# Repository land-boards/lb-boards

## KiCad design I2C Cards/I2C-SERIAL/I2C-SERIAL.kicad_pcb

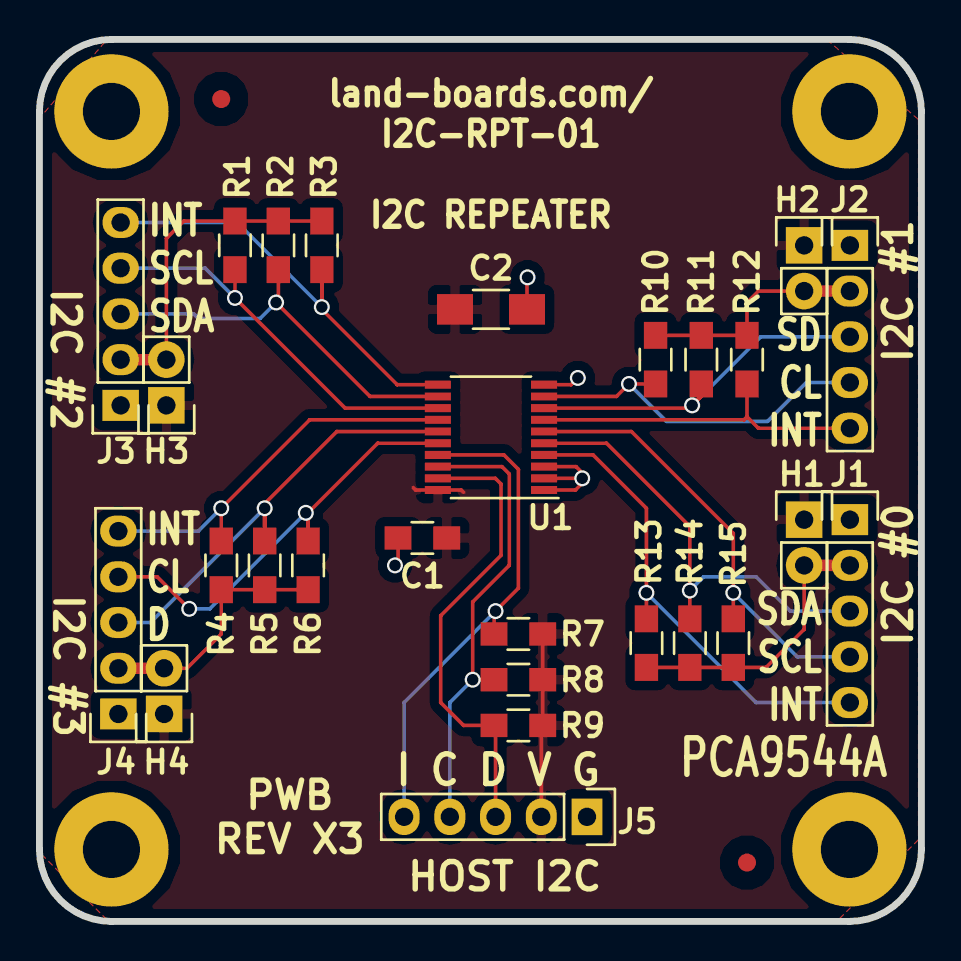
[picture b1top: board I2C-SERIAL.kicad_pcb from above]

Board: 2 copper layers, 49.0 x 49.0 mm, 35 parts (1 on the bottom side), 21 nets.

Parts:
C1: 0.1uF; R_0805_HandSoldering
C2: 0.1uF; R_1206_HandSoldering
FID1, FID2: ADAFRUIT_FIDUCIAL; FIDUCIAL
H1, H2, H3, H4: CONN_01X02; Pin_Header_Straight_1x02
J1, J2, J3, J4, J5: I2CINT-5PIN; Pin_Header_Straight_1x05
MTG1, MTG2, MTG3, MTG4: MTG_HOLE; MTG-4-40
R1, R2, R3, R4, R5, R6, R7, R8, R9, R10, R11, R12, R13, R14, R15: 3.3K; R_0805_HandSoldering
ST1: CONN_1; REV_BLOCK
TESTED: VAL**; TEST_BLK-REAR
U1: PCA9544A; TSSOP-20_4.4x6.5mm_Pitch0.65mm

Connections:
/PWR: C1.1, C2.1, H1.1, H2.1, H3.1, H4.1, J5.2, R7.1, R8.1, R9.1, U1.20
/SCK0: J1.4, R15.2, U1.6
/SCK1: J2.4, R10.2, U1.9
/SCK2: J3.4, R1.2, U1.13
/SCK3: J4.4, R6.2, U1.16
/SDA0: J1.3, R14.2, U1.5
/SDA1: J2.3, R11.2, U1.8
/SDA2: J3.3, R2.2, U1.12
/SDA3: J4.3, R5.2, U1.15
/~I0: J1.5, R13.2, U1.4
/~I1: J2.5, R12.2, U1.7
/~I2: J3.5, R3.2, U1.11
/~I3: J4.5, R4.2, U1.14
/~IH: J5.5, R7.2, U1.17
GND: C1.2, C2.2, J1.1, J2.1, J3.1, J4.1, J5.1, U1.1, U1.2, U1.3, U1.10
unnamed: H1.2, J1.2, R13.1, R14.1, R15.1
unnamed: H2.2, J2.2, R10.1, R11.1, R12.1
unnamed: H3.2, J3.2, R1.1, R2.1, R3.1
unnamed: H4.2, J4.2, R4.1, R5.1, R6.1
unnamed: J5.3, R9.2, U1.19
unnamed: J5.4, R8.2, U1.18

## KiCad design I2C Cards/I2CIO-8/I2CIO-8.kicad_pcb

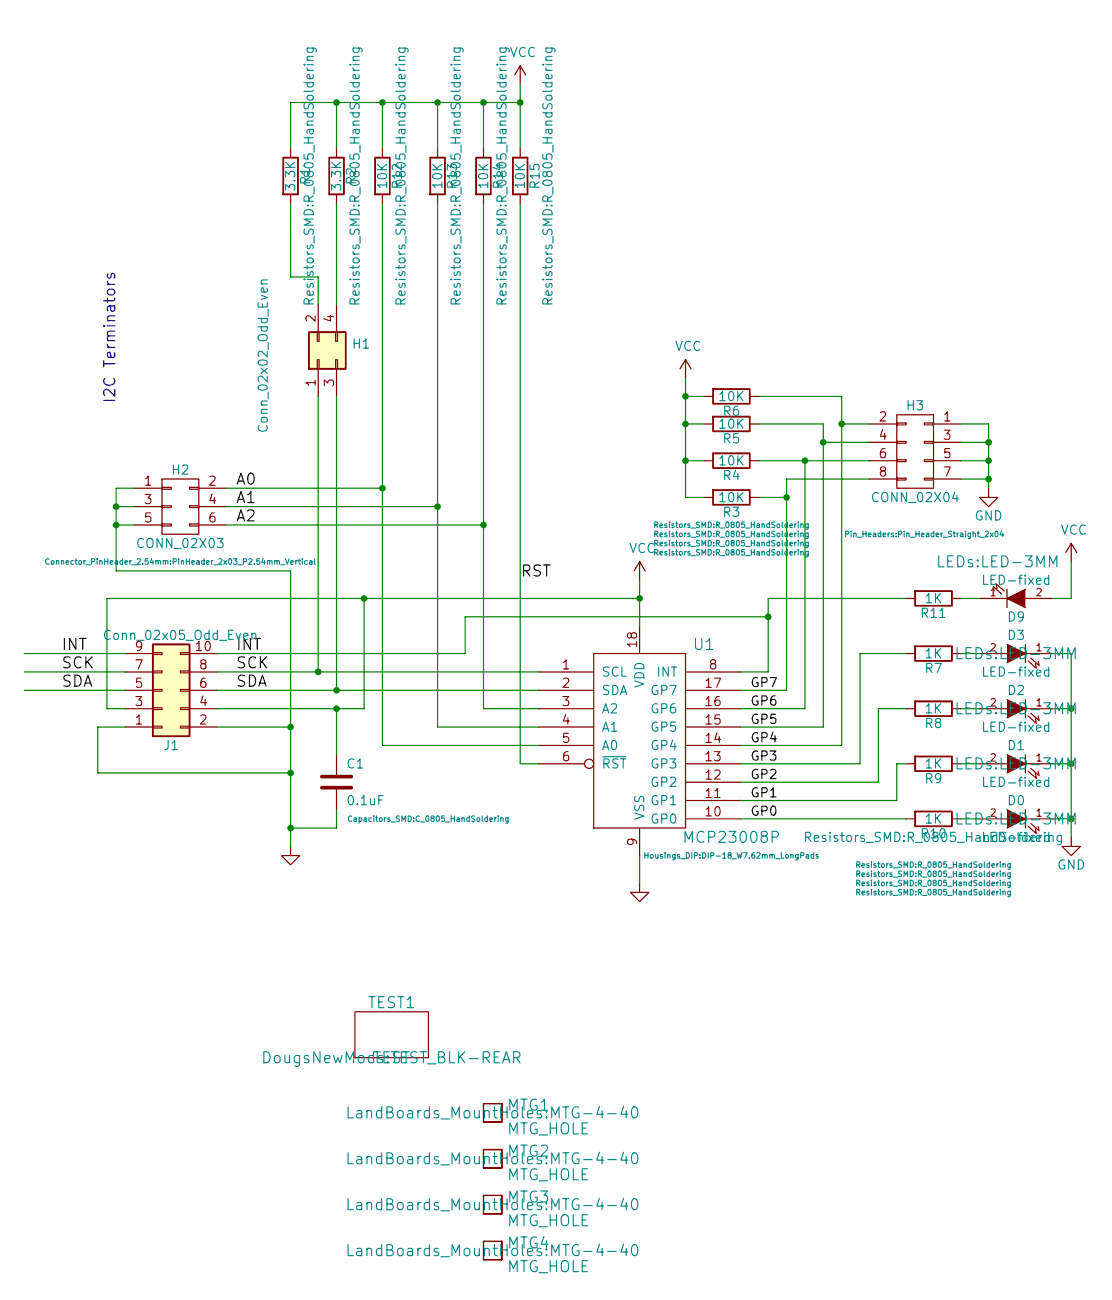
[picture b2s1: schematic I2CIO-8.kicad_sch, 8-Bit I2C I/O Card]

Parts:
C1: 0.1uF; C_0805_HandSoldering
D0, D1, D2, D3, D9: LED-fixed; LED-3MM
H1: Conn_02x02_Odd_Even; PinHeader_2x02_P2.54mm_Vertical
H2: CONN_02X03; PinHeader_2x03_P2.54mm_Vertical
H3: CONN_02X04; Pin_Header_Straight_2x04
J1: Conn_02x05_Odd_Even; PinHeader_2x05_P2.54mm_Horizontal
MTG1, MTG2, MTG3, MTG4: MTG_HOLE; MTG-4-40
R1, R2: 3.3K; R_0805_HandSoldering
R3, R4, R5, R6, R12, R13, R14, R15: 10K; R_0805_HandSoldering
R7, R8, R9, R10, R11: 1K; R_0805_HandSoldering
TEST1: TEST; TEST_BLK-REAR
U1: MCP23008P; DIP-18_W7.62mm_LongPads

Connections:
/A0: H2.2, R12.2, U1.5 (A0)
/A1: H2.4, R13.2, U1.4 (A1)
/A2: H2.6, R14.2, U1.3 (A2)
/GP0: R10.2, U1.10 (GP0)
/GP1: R9.2, U1.11 (GP1)
/GP2: R8.2, U1.12 (GP2)
/GP3: R7.2, U1.13 (GP3)
/GP4: H3.2, R6.1, U1.14 (GP4)
/GP5: H3.4, R5.1, U1.15 (GP5)
/GP6: H3.6, R4.1, U1.16 (GP6)
/GP7: H3.8, R3.1, U1.17 (GP7)
/INT: J1.9, J1.10, R11.2, U1.8 (INT)
/RST: R15.2, U1.6 (~RST)
/SCK: H1.1, J1.7, J1.8, U1.1 (SCL)
/SDA: H1.3, J1.5, J1.6, U1.2 (SDA)
GND: C1.2, D0.1 (K), D1.1 (K), D2.1 (K), D3.1 (K), H2.1, H2.3, H2.5, H3.1, H3.3, H3.5, H3.7, J1.1, J1.2, U1.9 (VSS)
unnamed: D0.2 (A), R10.1
unnamed: D1.2 (A), R9.1
unnamed: D2.2 (A), R8.1
unnamed: D3.2 (A), R7.1
unnamed: H1.2, R1.2
unnamed: H1.4, R2.2
unnamed: D9.1 (K), R11.1
VCC: C1.1, D9.2 (A), J1.3, J1.4, R1.1, R2.1, R3.2, R4.2, R5.2, R6.2, R12.1, R13.1, R14.1, R15.1, U1.18 (VDD)

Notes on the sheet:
I2C Terminators

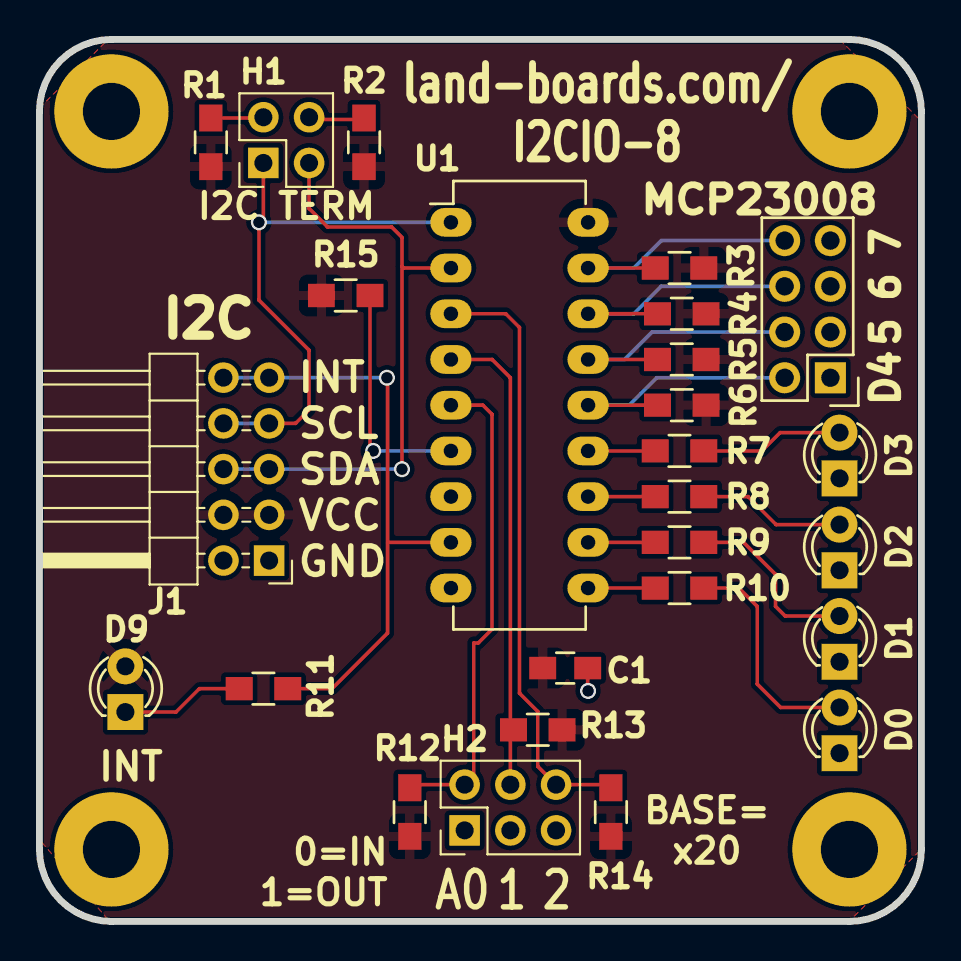
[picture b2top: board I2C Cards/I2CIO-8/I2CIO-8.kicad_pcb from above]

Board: 2 copper layers, 49.0 x 49.0 mm, 31 parts (0 on the bottom side), 24 nets.

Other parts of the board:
TEST: TEST; TEST_BLK-REAR

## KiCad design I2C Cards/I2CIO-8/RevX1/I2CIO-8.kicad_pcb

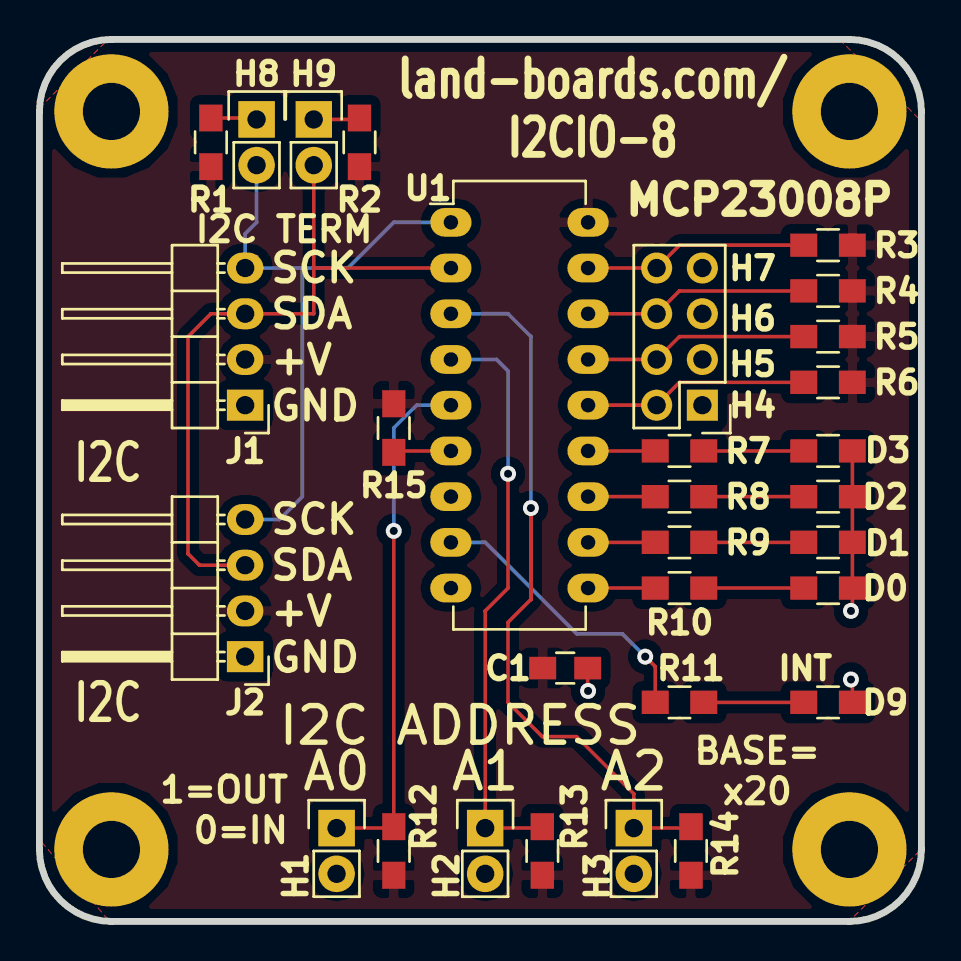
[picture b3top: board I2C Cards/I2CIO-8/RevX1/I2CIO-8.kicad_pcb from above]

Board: 2 copper layers, 49.0 x 49.0 mm, 35 parts (0 on the bottom side), 24 nets.

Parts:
C1: 0.1uF; C_0805_HandSoldering
D0, D1, D2, D3, D9: LED; R_0805_HandSoldering
H1, H2, H3, H8, H9: CONN_2; Pin_Header_Straight_1x02
H4: CONN_02X04; Pin_Header_Straight_2x04
J1, J2: CONN_4; Pin_Header_Angled_1x04
MTG5, MTG6, MTG7: MTG_HOLE; MTG-4-40
MTG?1: MTG_HOLE; MTG-4-40
R1, R2, R12, R13, R14, R15: 10K; R_0805_HandSoldering
R3, R4, R5, R6, R7, R8, R9, R10, R11: 330; R_0805_HandSoldering
TEST: TEST; TEST_BLK-REAR
U1: MCP23008P; DIP-18_W7.62mm_LongPads

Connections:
+5V: C1.1, J1.2, J2.2, R1.1, R2.1, R3.2, R4.2, R5.2, R6.2, R12.1, R13.1, R14.1, R15.1, U1.18
/A0: H1.1, R12.2, U1.5
/A1: H2.1, R13.2, U1.4
/A2: H3.1, R14.2, U1.3
/RST: R15.2, U1.6
/SCK: H8.2, J1.4, J2.4, U1.1
/SDA: H9.2, J1.3, J2.3, U1.2
GND: C1.2, D0.2, D1.2, D2.2, D3.2, D9.2, H1.2, H2.2, H3.2, H4.1, H4.3, H4.5, H4.7, J1.1, J2.1, U1.9
unnamed: D0.1, R10.1
unnamed: D1.1, R9.1
unnamed: D2.1, R8.1
unnamed: D3.1, R7.1
unnamed: D9.1, R11.1
unnamed: H8.1, R1.2
unnamed: H9.1, R2.2
unnamed: H4.2, R6.1, U1.14
unnamed: H4.4, R5.1, U1.15
unnamed: H4.6, R4.1, U1.16
unnamed: H4.8, R3.1, U1.17
unnamed: R7.2, U1.13
unnamed: R8.2, U1.12
unnamed: R9.2, U1.11
unnamed: R10.2, U1.10
unnamed: R11.2, U1.8

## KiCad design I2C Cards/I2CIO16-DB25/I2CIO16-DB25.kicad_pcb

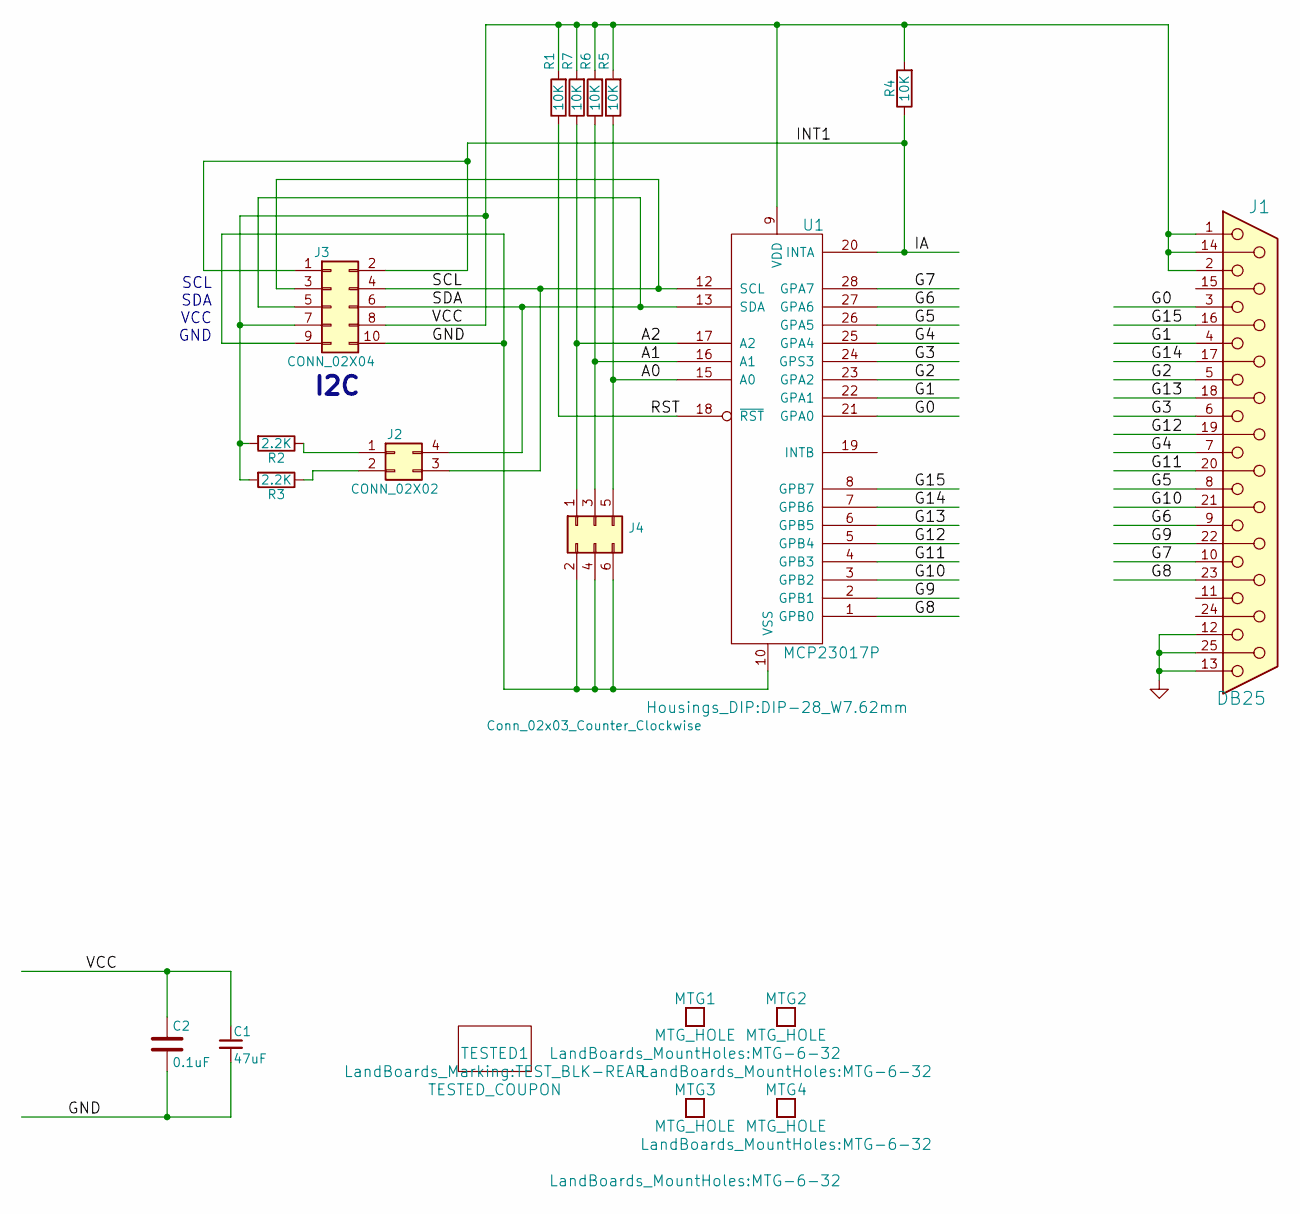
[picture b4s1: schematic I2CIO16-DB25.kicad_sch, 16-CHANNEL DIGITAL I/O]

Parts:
C1: 47uF; C_Radial_D5_L11_P2.5
C2: 0.1uF; C_Rect_L7_W2_P5
J1: DB25; DB25FC
J2: CONN_02X02; PinHeader_2x02_P2.54mm_Horizontal
J3: CONN_02X04; PinHeader_2x05_P2.54mm_Horizontal
J4: Conn_02x03_Counter_Clockwise; PinHeader_2x03_P2.54mm_Horizontal
MTG1, MTG2, MTG3, MTG4: MTG_HOLE; MTG-6-32
R1, R4, R5, R6, R7: 10K; R_Axial_DIN0207_L6.3mm_D2.5mm_P10.16mm_Horizontal
R2, R3: 2.2K; R_Axial_DIN0207_L6.3mm_D2.5mm_P10.16mm_Horizontal
TESTED1: TESTED_COUPON; TEST_BLK-REAR
U1: MCP23017P; DIP-28_W7.62mm

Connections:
/A0: J4.5, R5.1, U1.15 (A0)
/A1: J4.3, R6.1, U1.16 (A1)
/A2: J4.1, R7.1, U1.17 (A2)
/G0: J1.3, U1.21 (GPA0)
/G1: J1.4, U1.22 (GPA1)
/G2: J1.5, U1.23 (GPA2)
/G3: J1.6, U1.24 (GPS3)
/G4: J1.7, U1.25 (GPA4)
/G5: J1.8, U1.26 (GPA5)
/G6: J1.9, U1.27 (GPA6)
/G7: J1.10, U1.28 (GPA7)
/G8: J1.23, U1.1 (GPB0)
/G9: J1.22, U1.2 (GPB1)
/G10: J1.21, U1.3 (GPB2)
/G11: J1.20, U1.4 (GPB3)
/G12: J1.19, U1.5 (GPB4)
/G13: J1.18, U1.6 (GPB5)
/G14: J1.17, U1.7 (GPB6)
/G15: J1.16, U1.8 (GPB7)
/IA: J3.1, J3.2, R4.1, U1.20 (INTA)
/RST: R1.1, U1.18 (~RST)
/SCL: J2.3, J3.3, J3.4, U1.12 (SCL)
/SDA: J2.4, J3.5, J3.6, U1.13 (SDA)
/VCC: C1.1, C2.1, J1.1, J1.2, J1.14, J3.7, J3.8, R1.2, R2.2, R3.2, R4.2, R5.2, R6.2, R7.2, U1.9 (VDD)
GND: C1.2, C2.2, J1.12, J1.13, J1.25, J3.9, J3.10, J4.2, J4.4, J4.6, U1.10 (VSS)
unnamed: J2.1, R2.1
unnamed: J2.2, R3.1

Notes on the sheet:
SCL SDA VCC GND
I2C

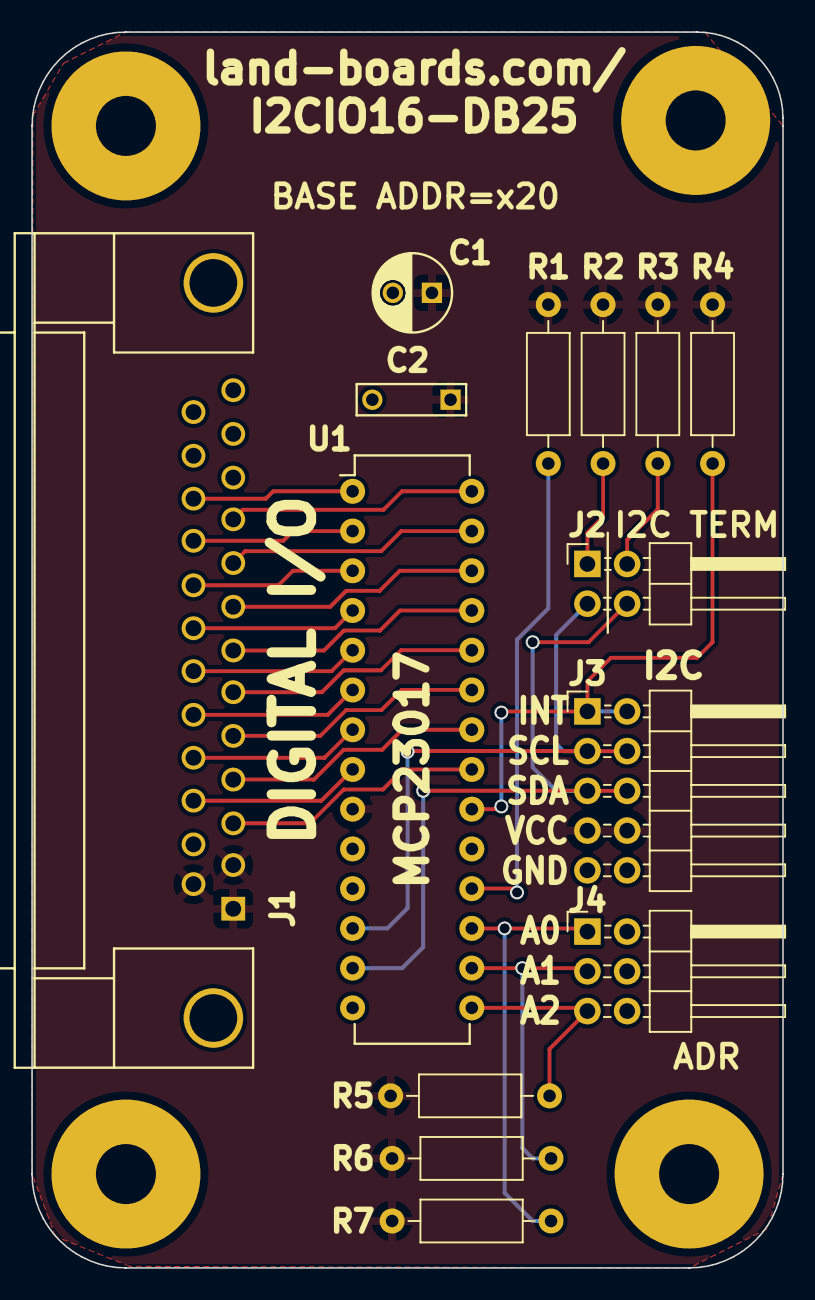
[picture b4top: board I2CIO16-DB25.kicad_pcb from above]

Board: 2 copper layers, 48.0 x 79.0 mm, 19 parts (0 on the bottom side), 27 nets.

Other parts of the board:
TESTED: TESTED_COUPON; TEST_BLK-REAR

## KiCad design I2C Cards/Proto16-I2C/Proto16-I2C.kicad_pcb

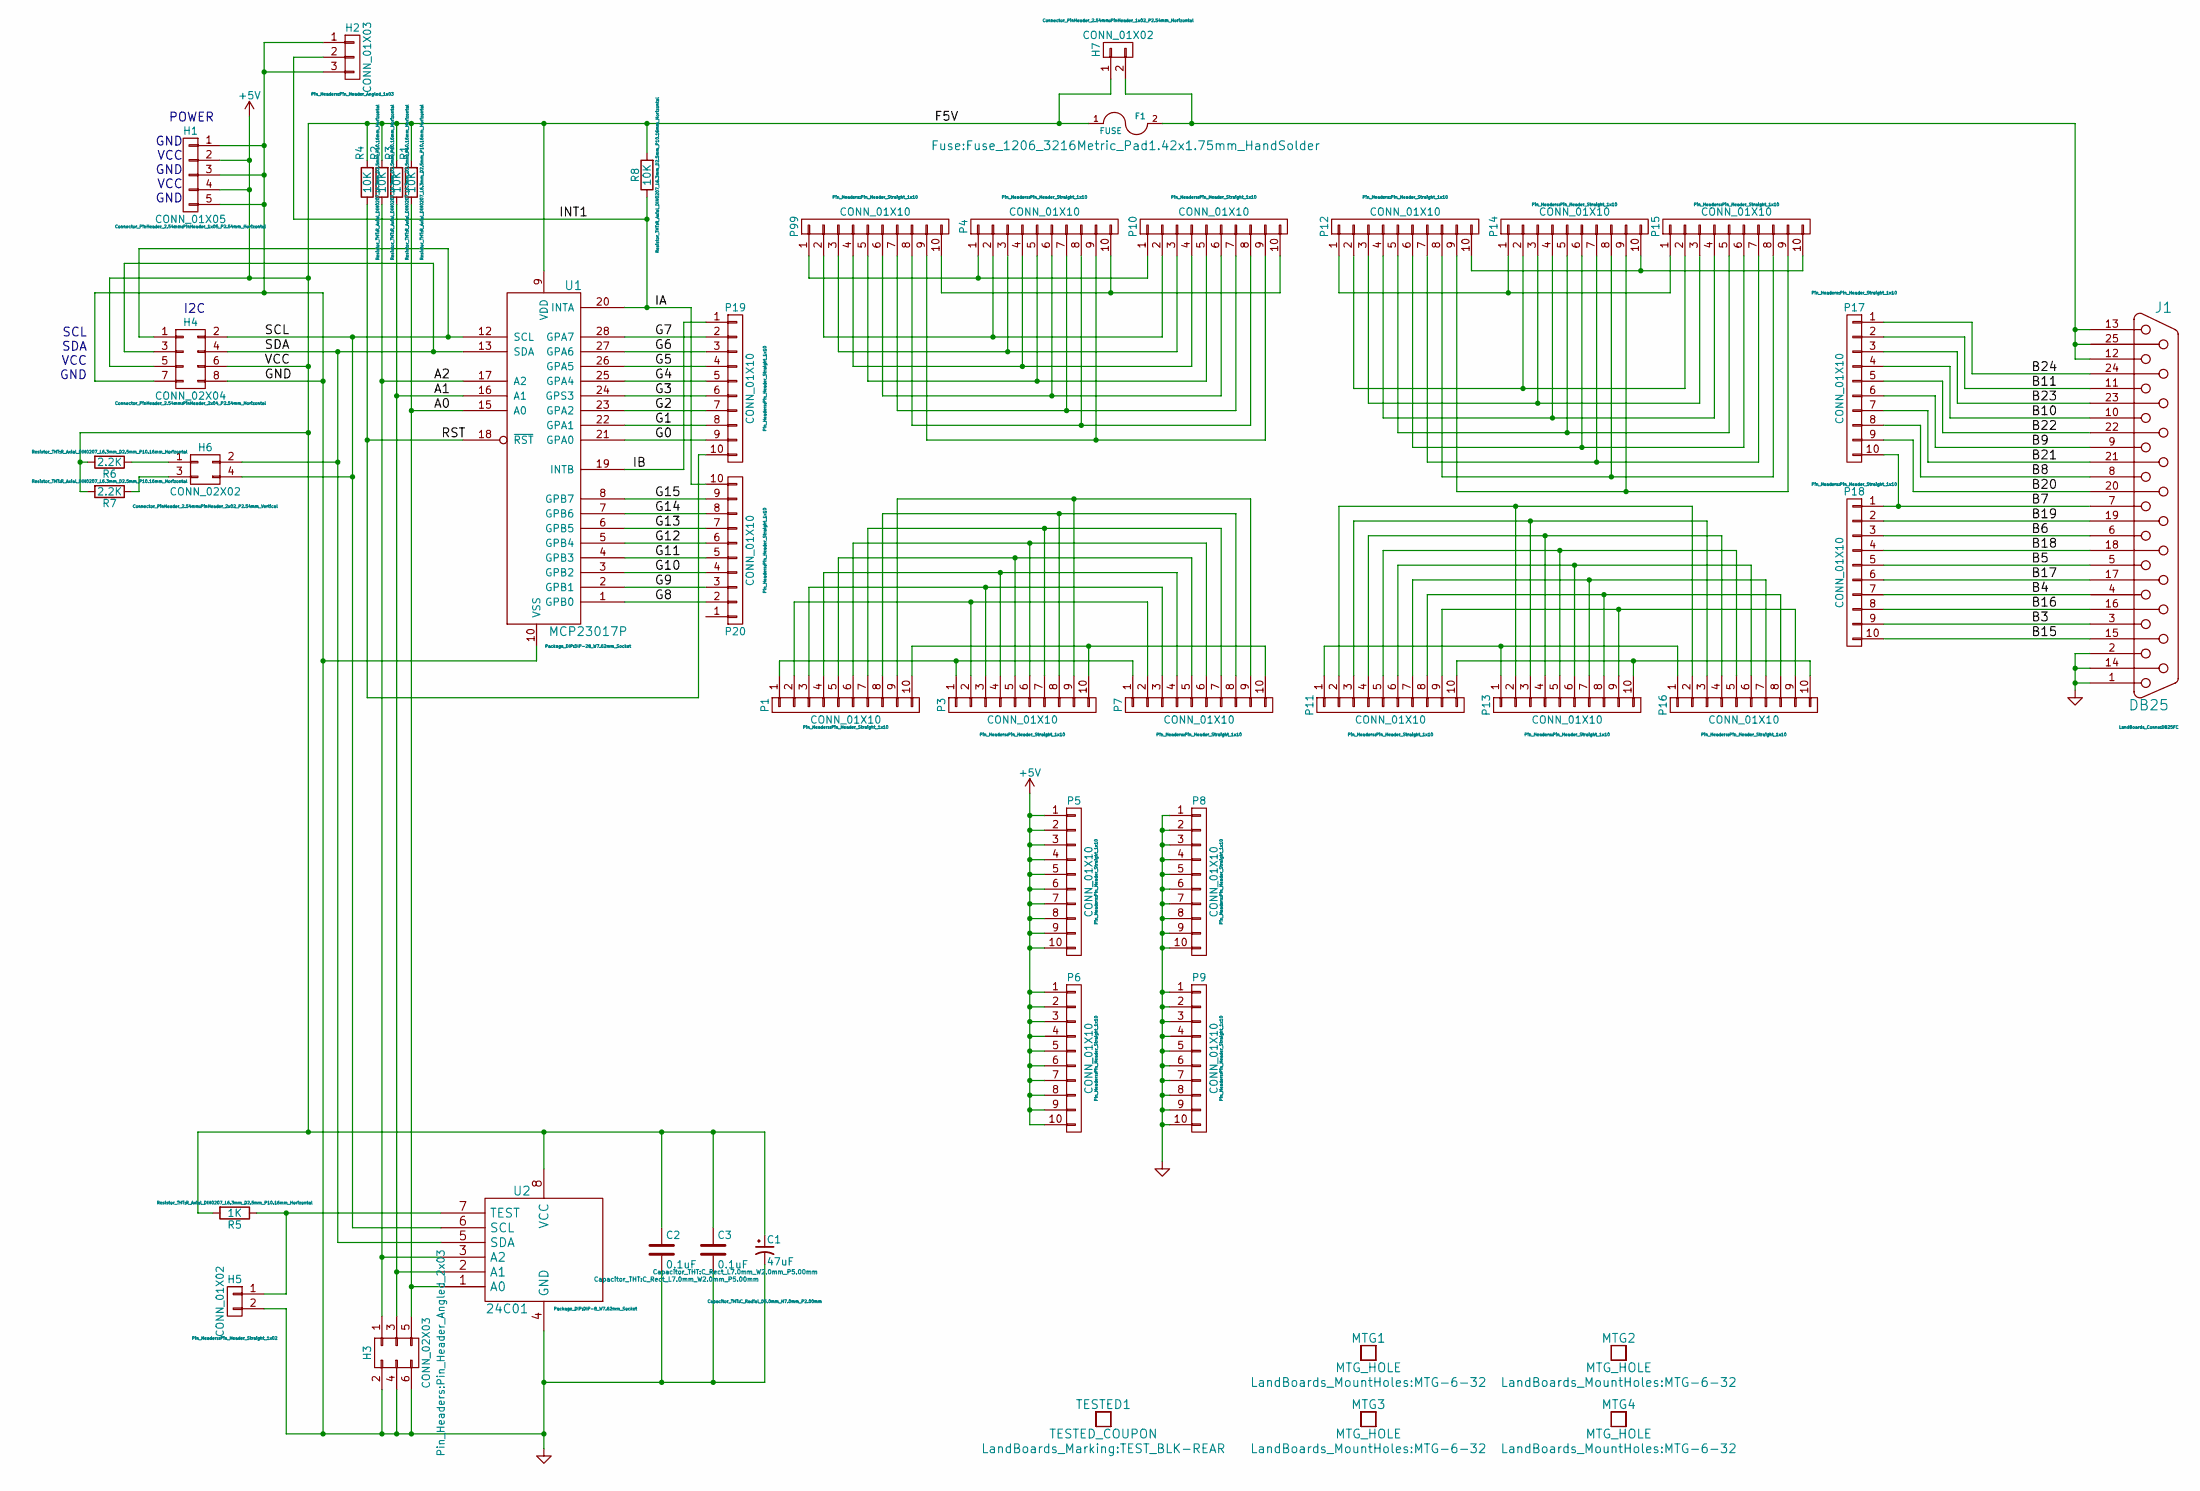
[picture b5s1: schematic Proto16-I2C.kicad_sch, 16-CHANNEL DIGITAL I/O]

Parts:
C1: 47uF; C_Radial_D5.0mm_H7.0mm_P2.00mm
C2, C3: 0.1uF; C_Rect_L7.0mm_W2.0mm_P5.00mm
F1: FUSE; Fuse_1206_3216Metric_Pad1.42x1.75mm_HandSolder
H1: CONN_01X05; PinHeader_1x05_P2.54mm_Horizontal
H2: CONN_01X03; Pin_Header_Angled_1x03
H3: CONN_02X03; Pin_Header_Angled_2x03
H4: CONN_02X04; PinHeader_2x04_P2.54mm_Horizontal
H5: CONN_01X02; Pin_Header_Straight_1x02
H6: CONN_02X02; PinHeader_2x02_P2.54mm_Vertical
H7: CONN_01X02; PinHeader_1x02_P2.54mm_Horizontal
J1: DB25; DB25FC
MTG1, MTG2, MTG3, MTG4: MTG_HOLE; MTG-6-32
P1, P3, P4, P5, P6, P7, P8, P9, P10, P11, P12, P13, P14, P15, P16, P17, P18, P19, P20, P99: CONN_01X10; Pin_Header_Straight_1x10
R1, R2, R3, R4, R8: 10K; R_Axial_DIN0207_L6.3mm_D2.5mm_P10.16mm_Horizontal
R5: 1K; R_Axial_DIN0207_L6.3mm_D2.5mm_P10.16mm_Horizontal
R6, R7: 2.2K; R_Axial_DIN0207_L6.3mm_D2.5mm_P10.16mm_Horizontal
TESTED1: TESTED_COUPON; TEST_BLK-REAR
U1: MCP23017P; DIP-28_W7.62mm_Socket
U2: 24C01; DIP-8_W7.62mm_Socket

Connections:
+5V: C1.1, C2.1, C3.1, F1.1, H1.2, H1.4, H4.5, H4.6, H7.1, P5.1, P5.2, P5.3, P5.4, P5.5, P5.6, P5.7, P5.8, P5.9, P5.10, P6.1, P6.2, P6.3, P6.4, P6.5, P6.6, P6.7, P6.8, P6.9, P6.10, R1.2, R2.2, R3.2, R4.2, R5.2, R6.2, R7.2, R8.2, U1.9 (VDD), U2.8 (VCC)
/A0: H3.5, R1.1, U1.15 (A0), U2.1 (A0)
/A1: H3.3, R3.1, U1.16 (A1), U2.2 (A1)
/A2: H3.1, R2.1, U1.17 (A2), U2.3 (A2)
/B3: J1.3, P18.9
/B4: J1.4, P18.7
/B5: J1.5, P18.5
/B6: J1.6, P18.3
/B7: J1.7, P17.10, P18.1
/B8: J1.8, P17.8
/B9: J1.9, P17.6
/B10: J1.10, P17.4
/B11: J1.11, P17.2
/B15: J1.15, P18.10
/B16: J1.16, P18.8
/B17: J1.17, P18.6
/B18: J1.18, P18.4
/B19: J1.19, P18.2
/B20: J1.20, P17.9
/B21: J1.21, P17.7
/B22: J1.22, P17.5
/B23: J1.23, P17.3
/B24: J1.24, P17.1
/G0: P19.9, U1.21 (GPA0)
/G1: P19.8, U1.22 (GPA1)
/G2: P19.7, U1.23 (GPA2)
/G3: P19.6, U1.24 (GPS3)
/G4: P19.5, U1.25 (GPA4)
/G5: P19.4, U1.26 (GPA5)
/G6: P19.3, U1.27 (GPA6)
/G7: P19.2, U1.28 (GPA7)
/G8: P20.2, U1.1 (GPB0)
/G9: P20.3, U1.2 (GPB1)
/G10: P20.4, U1.3 (GPB2)
/G11: P20.5, U1.4 (GPB3)
/G12: P20.6, U1.5 (GPB4)
/G13: P20.7, U1.6 (GPB5)
/G14: P20.8, U1.7 (GPB6)
/G15: P20.9, U1.8 (GPB7)
/IA: H2.2, P20.10, R8.1, U1.20 (INTA)
/IB: P19.1, U1.19 (INTB)
/RST: P19.10, R4.1, U1.18 (~RST)
/SCL: H4.1, H4.2, H6.4, U1.12 (SCL), U2.6 (SCL)
/SDA: H4.3, H4.4, H6.2, U1.13 (SDA), U2.5 (SDA)
GND: C1.2, C2.2, C3.2, H1.1, H1.3, H1.5, H2.1, H2.3, H3.2, H3.4, H3.6, H4.7, H4.8, H5.2, J1.1, J1.2, J1.14, P8.1, P8.2, P8.3, P8.4, P8.5, P8.6, P8.7, P8.8, P8.9, P8.10, P9.1, P9.2, P9.3, P9.4, P9.5, P9.6, P9.7, P9.8, P9.9, P9.10, U1.10 (VSS), U2.4 (GND)
unnamed: F1.2, H7.2, J1.12, J1.13, J1.25
unnamed: H5.1, R5.1, U2.7 (TEST)
unnamed: H6.1, R6.1
unnamed: H6.3, R7.1
unnamed: P1.1, P3.1, P7.1
unnamed: P1.2, P3.2, P7.2
unnamed: P1.3, P3.3, P7.3
unnamed: P1.4, P3.4, P7.4
unnamed: P1.5, P3.5, P7.5
unnamed: P1.6, P3.6, P7.6
unnamed: P1.7, P3.7, P7.7
unnamed: P1.9, P3.9, P7.9
unnamed: P1.10, P3.10, P7.10
unnamed: P1.8, P3.8, P7.8
unnamed: P4.3, P10.3, P99.3
unnamed: P4.4, P10.4, P99.4
unnamed: P4.5, P10.5, P99.5
unnamed: P4.6, P10.6, P99.6
unnamed: P4.7, P10.7, P99.7
unnamed: P4.8, P10.8, P99.8
unnamed: P4.1, P10.1, P99.1
unnamed: P4.2, P10.2, P99.2
unnamed: P4.9, P10.9, P99.9
unnamed: P4.10, P10.10, P99.10
unnamed: P11.1, P13.1, P16.1
unnamed: P11.3, P13.3, P16.3
unnamed: P11.4, P13.4, P16.4
unnamed: P11.5, P13.5, P16.5
unnamed: P11.6, P13.6, P16.6
unnamed: P11.7, P13.7, P16.7
unnamed: P11.8, P13.8, P16.8
unnamed: P11.9, P13.9, P16.9
unnamed: P11.10, P13.10, P16.10
unnamed: P12.1, P14.1, P15.1
unnamed: P12.2, P14.2, P15.2
unnamed: P12.3, P14.3, P15.3
unnamed: P12.4, P14.4, P15.4
unnamed: P12.5, P14.5, P15.5
unnamed: P12.6, P14.6, P15.6
unnamed: P12.7, P14.7, P15.7
unnamed: P12.8, P14.8, P15.8
unnamed: P12.9, P14.9, P15.9
unnamed: P12.10, P14.10, P15.10
unnamed: P11.2, P13.2, P16.2

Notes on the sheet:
SCL SDA VCC GND
POWER
GND VCC GND VCC GND
I2C

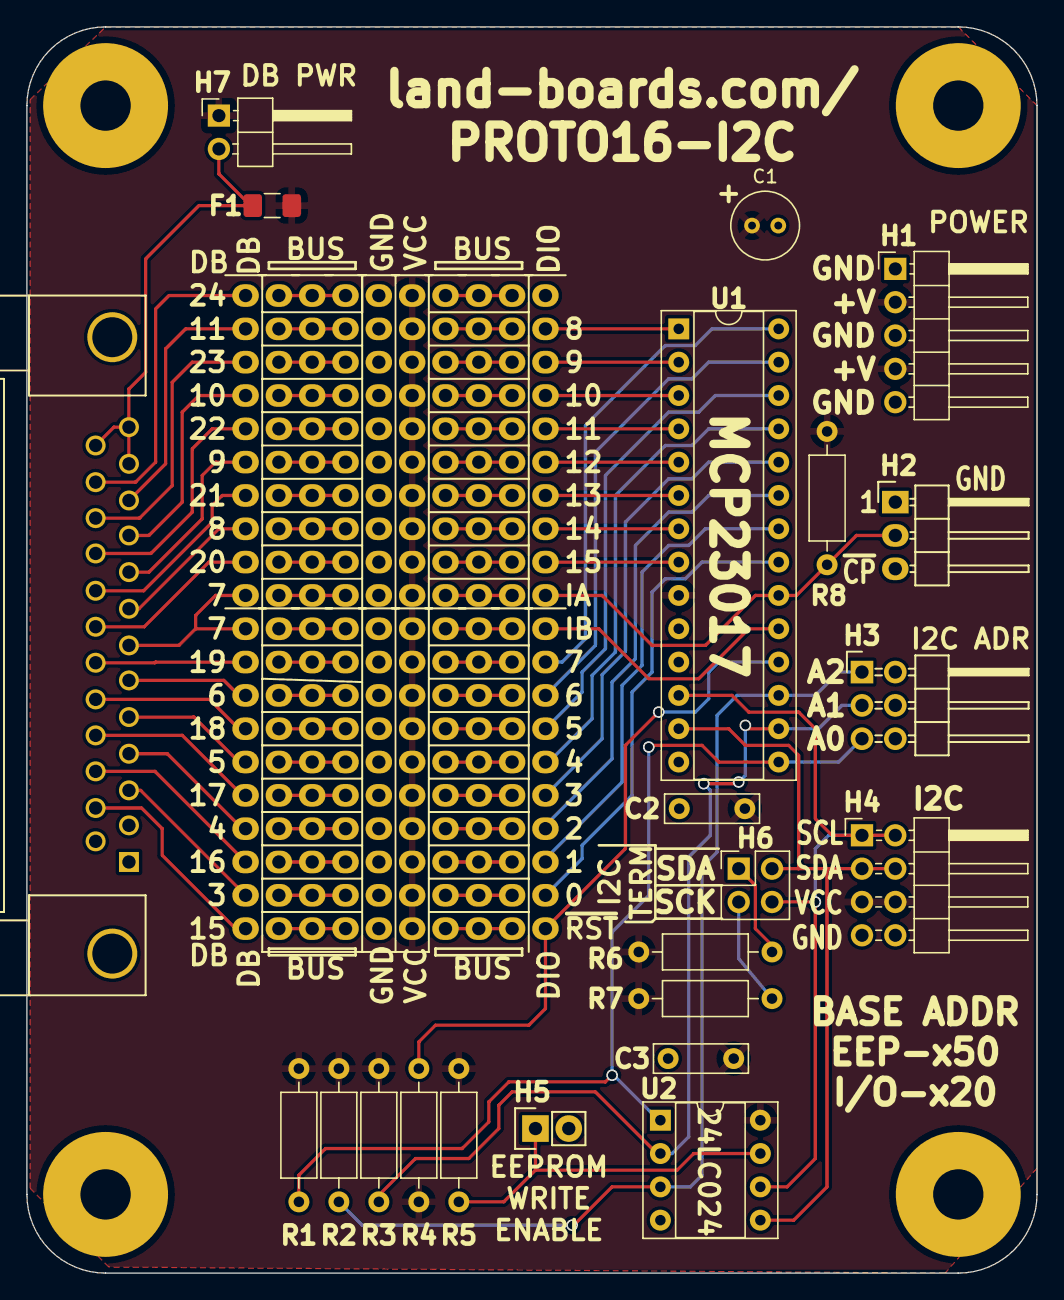
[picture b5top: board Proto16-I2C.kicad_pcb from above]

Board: 2 copper layers, 77.0 x 95.0 mm, 47 parts (0 on the bottom side), 89 nets.

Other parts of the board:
TESTED: TESTED_COUPON; TEST_BLK-REAR

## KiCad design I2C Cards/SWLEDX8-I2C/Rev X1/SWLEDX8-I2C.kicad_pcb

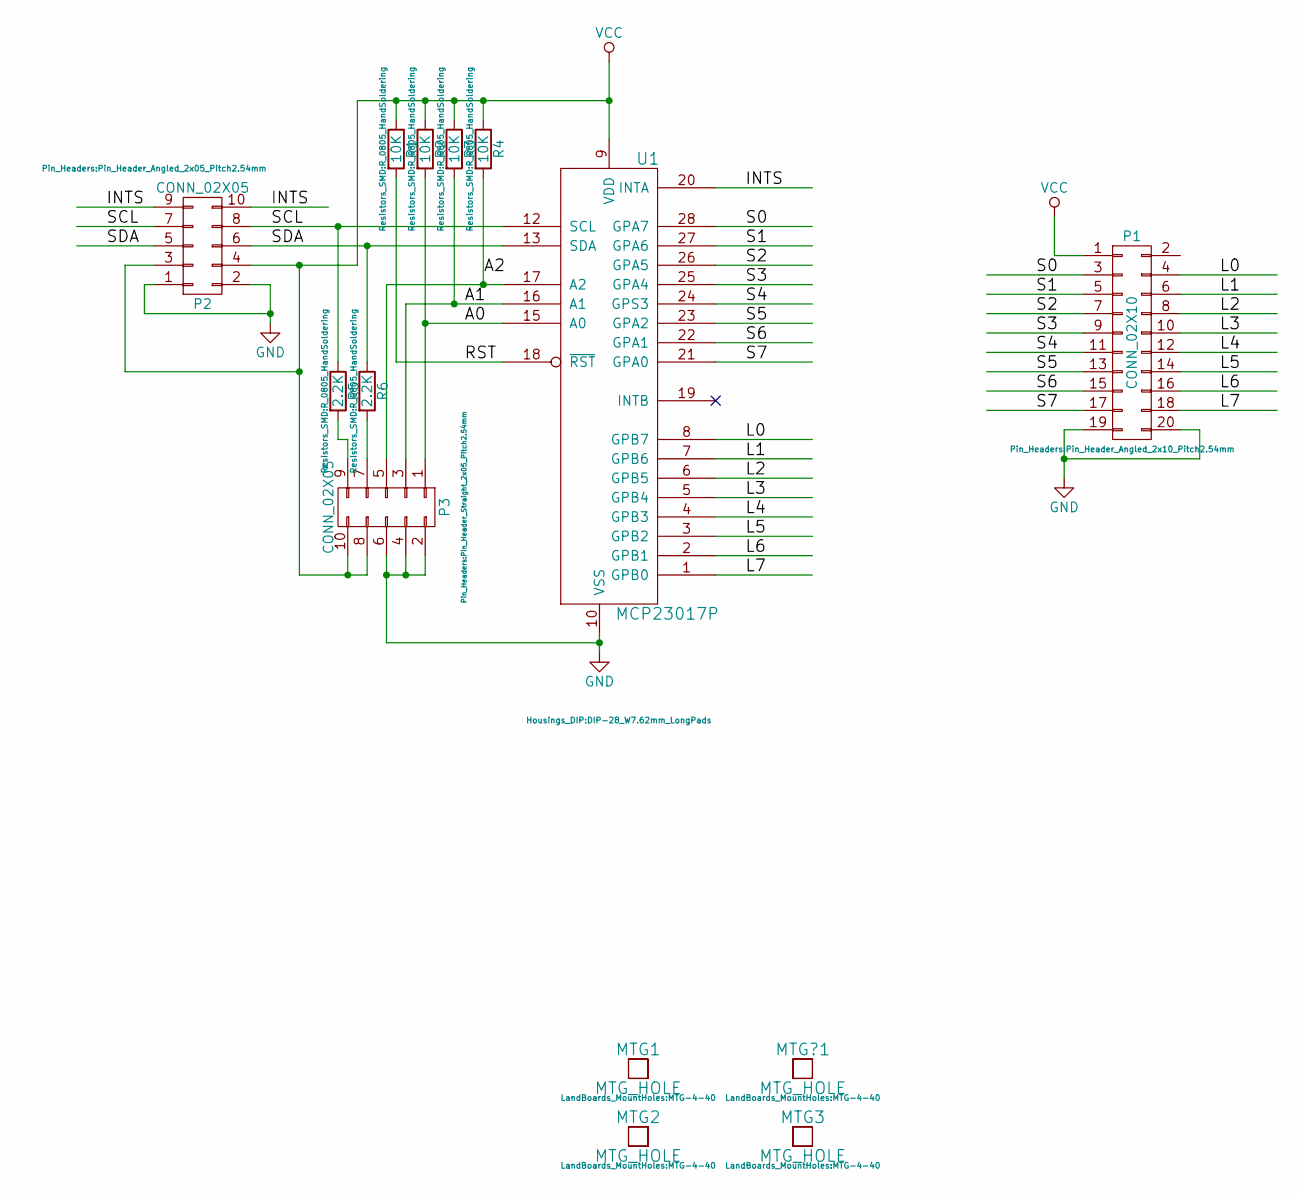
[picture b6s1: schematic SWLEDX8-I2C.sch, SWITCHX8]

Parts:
MTG1, MTG2, MTG3: MTG_HOLE; MTG-4-40
MTG?1: MTG_HOLE; MTG-4-40
P1: CONN_02X10; Pin_Header_Angled_2x10_Pitch2.54mm
P2: CONN_02X05; Pin_Header_Angled_2x05_Pitch2.54mm
P3: CONN_02X05; Pin_Header_Straight_2x05_Pitch2.54mm
R1, R2, R3, R4: 10K; R_0805_HandSoldering
R5, R6: 2.2K; R_0805_HandSoldering
U1: MCP23017P; DIP-28_W7.62mm_LongPads

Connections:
/A0: P3.1, R2.2, U1.15 (A0)
/A1: P3.3, R3.2, U1.16 (A1)
/A2: P3.5, R4.2, U1.17 (A2)
/INTS: P2.9, P2.10, U1.20 (INTA)
/L0: P1.4, U1.8 (GPB7)
/L1: P1.6, U1.7 (GPB6)
/L2: P1.8, U1.6 (GPB5)
/L3: P1.10, U1.5 (GPB4)
/L4: P1.12, U1.4 (GPB3)
/L5: P1.14, U1.3 (GPB2)
/L6: P1.16, U1.2 (GPB1)
/L7: P1.18, U1.1 (GPB0)
/RST: R1.2, U1.18 (~RST)
/S0: P1.3, U1.28 (GPA7)
/S1: P1.5, U1.27 (GPA6)
/S2: P1.7, U1.26 (GPA5)
/S3: P1.9, U1.25 (GPA4)
/S4: P1.11, U1.24 (GPS3)
/S5: P1.13, U1.23 (GPA2)
/S6: P1.15, U1.22 (GPA1)
/S7: P1.17, U1.21 (GPA0)
/SCL: P2.7, P2.8, R5.1, U1.12 (SCL)
/SDA: P2.5, P2.6, R6.1, U1.13 (SDA)
GND: P1.19, P1.20, P2.1, P2.2, P3.2, P3.4, P3.6, U1.10 (VSS)
unnamed: P3.7, R6.2
unnamed: P3.9, R5.2
VCC: P1.1, P2.3, P2.4, P3.8, P3.10, R1.1, R2.1, R3.1, R4.1, U1.9 (VDD)

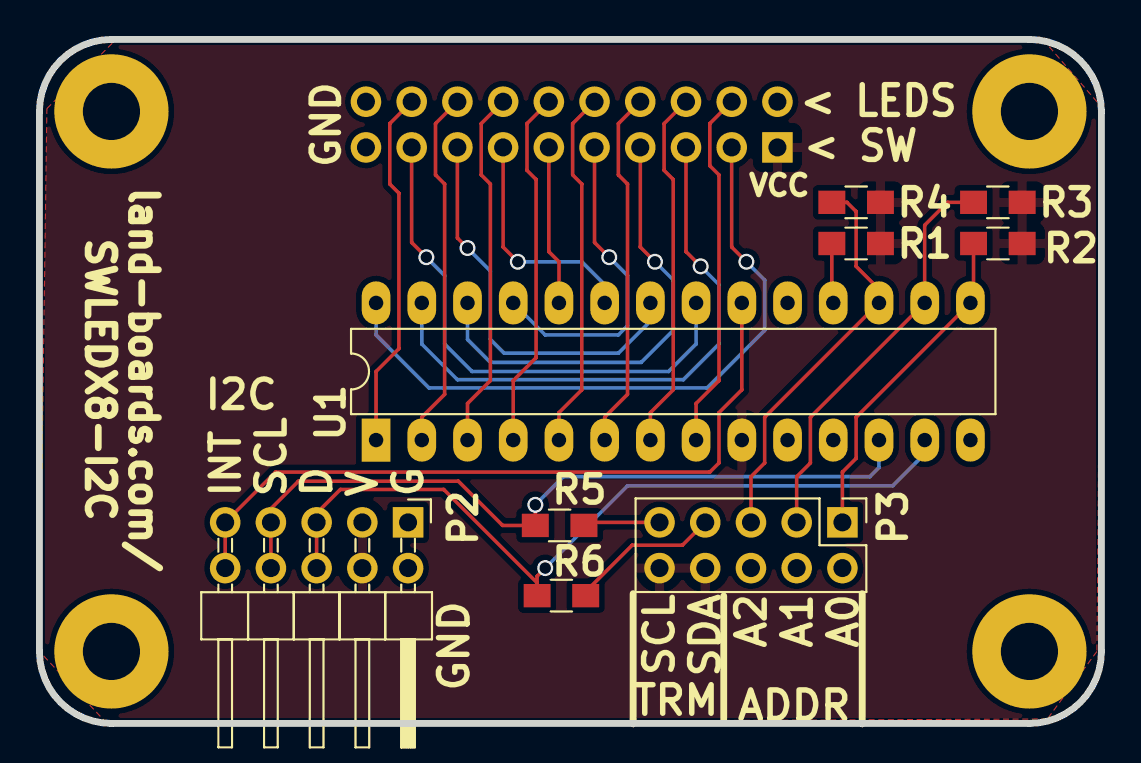
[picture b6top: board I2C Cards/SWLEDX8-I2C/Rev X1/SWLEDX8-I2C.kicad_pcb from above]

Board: 2 copper layers, 59.0 x 38.0 mm, 14 parts (1 on the bottom side), 27 nets.

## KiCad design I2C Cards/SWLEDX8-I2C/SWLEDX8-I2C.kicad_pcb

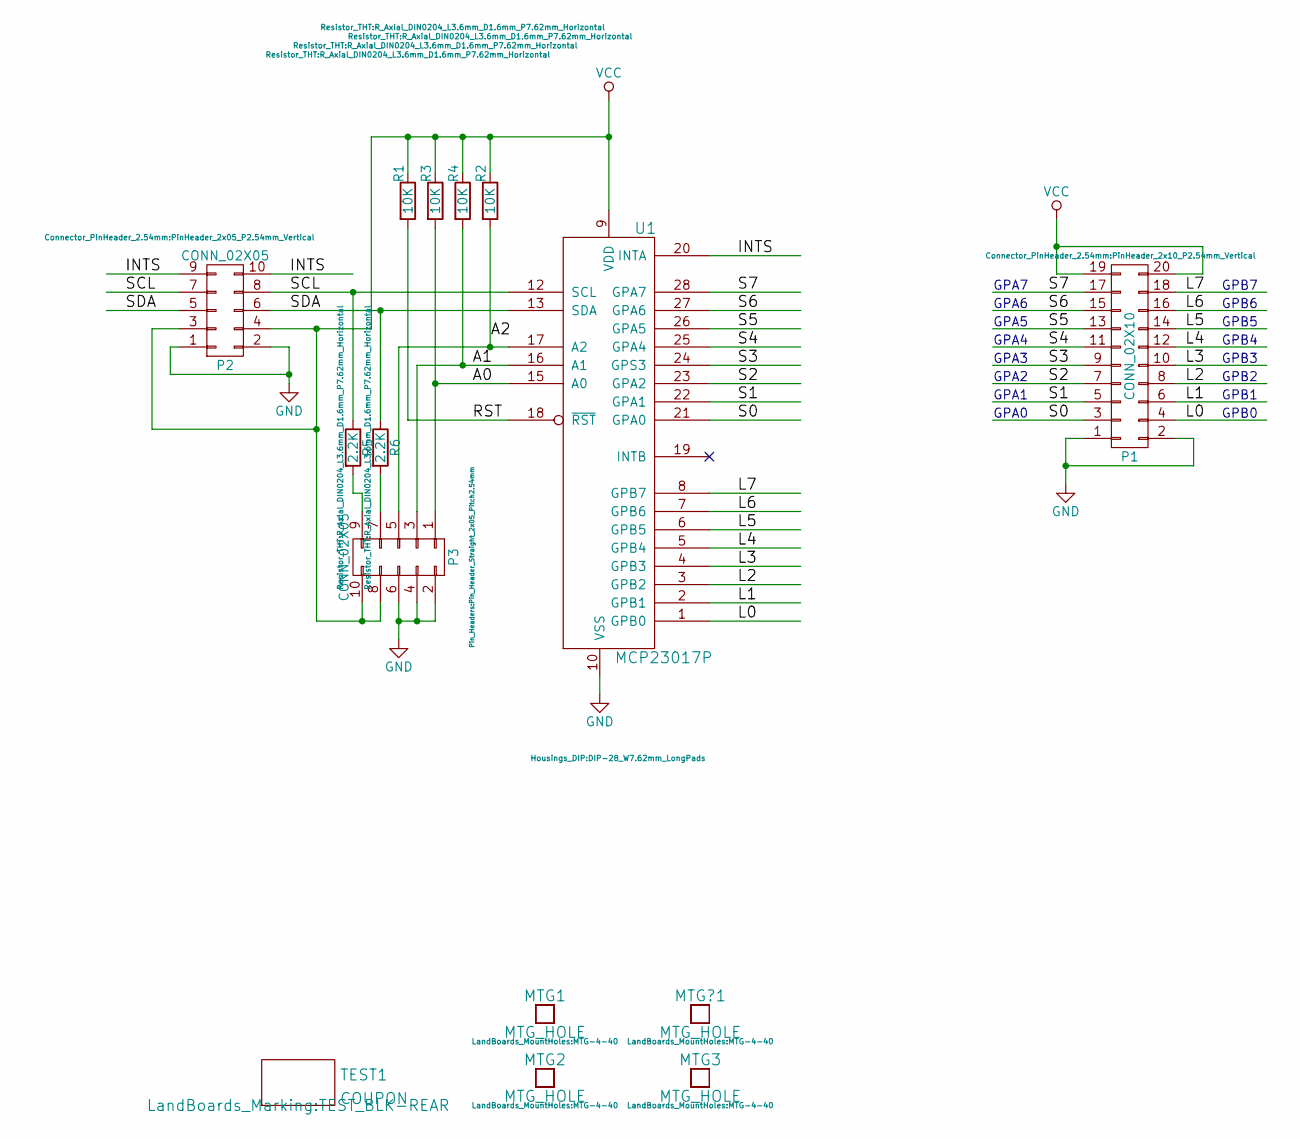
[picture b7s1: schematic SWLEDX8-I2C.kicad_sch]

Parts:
MTG1, MTG2, MTG3: MTG_HOLE; MTG-4-40
MTG?1: MTG_HOLE; MTG-4-40
P1: CONN_02X10; PinHeader_2x10_P2.54mm_Vertical
P2: CONN_02X05; PinHeader_2x05_P2.54mm_Vertical
P3: CONN_02X05; Pin_Header_Straight_2x05_Pitch2.54mm
R1, R2, R3, R4: 10K; R_Axial_DIN0204_L3.6mm_D1.6mm_P7.62mm_Horizontal
R5, R6: 2.2K; R_Axial_DIN0204_L3.6mm_D1.6mm_P7.62mm_Horizontal
TEST1: COUPON; TEST_BLK-REAR
U1: MCP23017P; DIP-28_W7.62mm_LongPads

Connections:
/A0: P3.1, R3.2, U1.15 (A0)
/A1: P3.3, R4.2, U1.16 (A1)
/A2: P3.5, R2.2, U1.17 (A2)
/INTS: P2.9, P2.10, U1.20 (INTA)
/L0: P1.4, U1.1 (GPB0)
/L1: P1.6, U1.2 (GPB1)
/L2: P1.8, U1.3 (GPB2)
/L3: P1.10, U1.4 (GPB3)
/L4: P1.12, U1.5 (GPB4)
/L5: P1.14, U1.6 (GPB5)
/L6: P1.16, U1.7 (GPB6)
/L7: P1.18, U1.8 (GPB7)
/RST: R1.2, U1.18 (~RST)
/S0: P1.3, U1.21 (GPA0)
/S1: P1.5, U1.22 (GPA1)
/S2: P1.7, U1.23 (GPA2)
/S3: P1.9, U1.24 (GPS3)
/S4: P1.11, U1.25 (GPA4)
/S5: P1.13, U1.26 (GPA5)
/S6: P1.15, U1.27 (GPA6)
/S7: P1.17, U1.28 (GPA7)
/SCL: P2.7, P2.8, R5.1, U1.12 (SCL)
/SDA: P2.5, P2.6, R6.1, U1.13 (SDA)
unnamed: P3.7, R6.2
unnamed: P3.9, R5.2
VCC: P1.19, P1.20, P2.3, P2.4, P3.8, P3.10, R1.1, R2.1, R3.1, R4.1, U1.9 (VDD)

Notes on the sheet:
GPB4
GPA0
GPB0
GPB3
GPA3
GPB1
GPA2
GPB2
GPA1
GPA5
GPA4
GPB6
GPB7
GPB5
GPA6
GPA7

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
